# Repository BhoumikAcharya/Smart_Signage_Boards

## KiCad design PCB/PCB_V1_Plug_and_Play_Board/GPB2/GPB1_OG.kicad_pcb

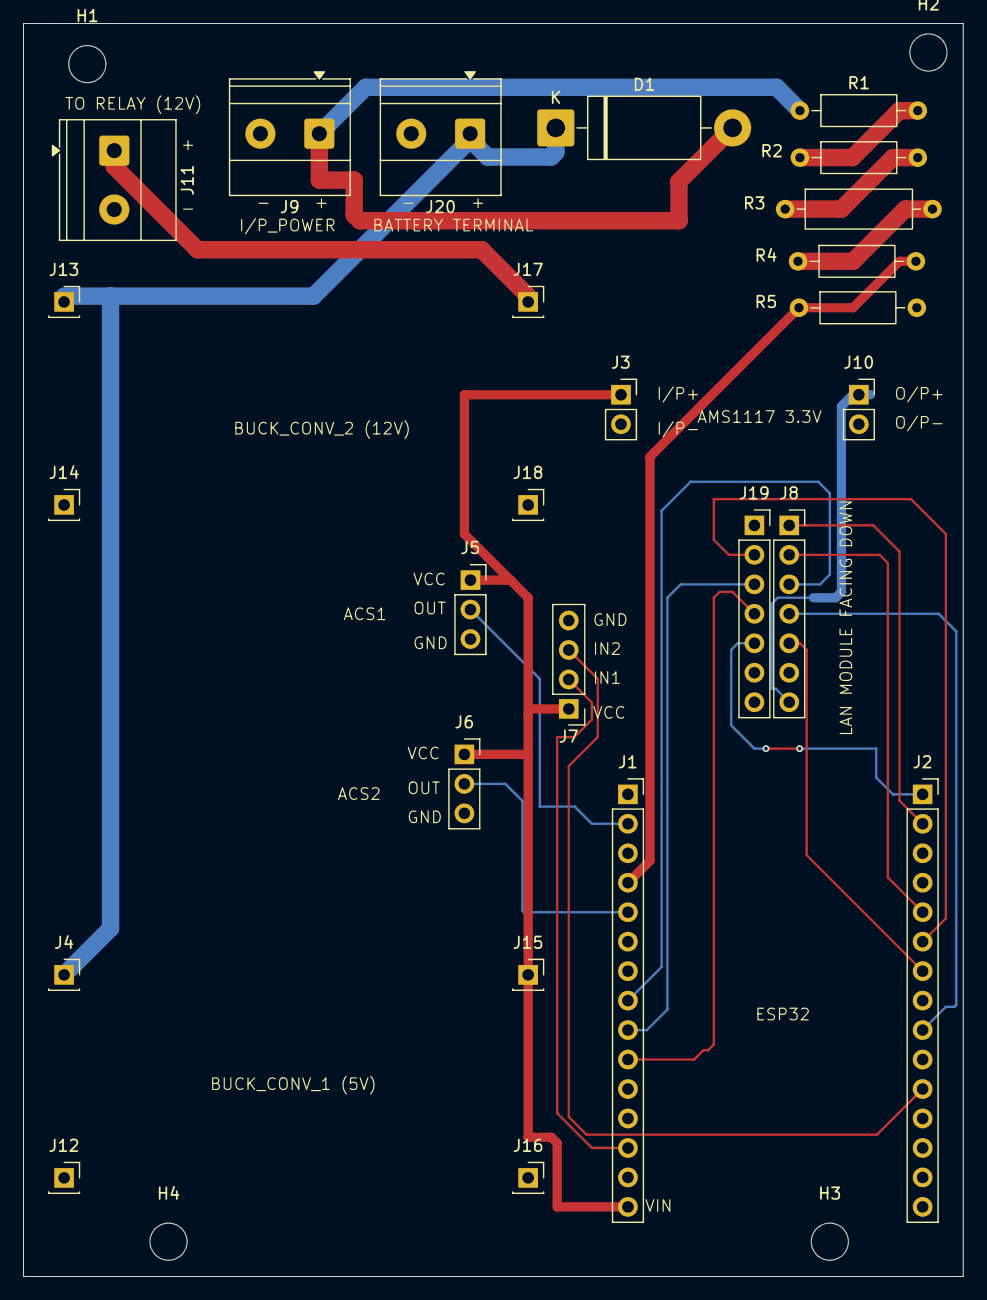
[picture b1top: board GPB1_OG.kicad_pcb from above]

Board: 2 copper layers, 81.0 x 108.0 mm, 30 parts (0 on the bottom side), 22 nets.

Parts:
D1: 1N5822; D_DO-201AD_P15.24mm_Horizontal
H1, H2, H3, H4: MountingScrew; MountingHole_3.2mm_M3
J1: ESP_Pins_1; PinSocket_1x15_P2.54mm_Vertical
J2: ESP_Pins_2; PinSocket_1x15_P2.54mm_Vertical
J3: AMS_I/P; PinSocket_1x02_P2.54mm_Vertical
J4: BC_I/P_+; PinSocket_1x01_P2.54mm_Vertical
J5: ACS712 1; PinSocket_1x03_P2.54mm_Vertical
J6: ACS712 2; PinSocket_1x03_P2.54mm_Vertical
J7: Relay; PinHeader_1x04_P2.54mm_Vertical
J8: LAN8720_Pins_1; PinSocket_1x07_P2.54mm_Vertical
J9, J20: I/P_TERMINAL; TerminalBlock_Phoenix_MKDS-1,5-2-5.08_1x02_P5.08mm_Horizont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
J10: AMS_O/P; PinSocket_1x02_P2.54mm_Vertical
J11: O/P Terminal; TerminalBlock_Phoenix_MKDS-1,5-2-5.08_1x02_P5.08mm_Horizont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
J12: BC1_I/P_GND; PinSocket_1x01_P2.54mm_Vertical
J13: BC2_I/P_+; PinSocket_1x01_P2.54mm_Vertical
J14: BC2_I/P_GND; PinSocket_1x01_P2.54mm_Vertical
J15: BC_O/P_+; PinSocket_1x01_P2.54mm_Vertical
J16: BC1_O/P_GND; PinSocket_1x01_P2.54mm_Vertical
J17: BC2_O/P_+; PinSocket_1x01_P2.54mm_Vertical
J18: BC2_O/P_GND; PinSocket_1x01_P2.54mm_Vertical
J19: LAN8720_Pins_2; PinSocket_1x07_P2.54mm_Vertical
R1, R2, R4, R5: 1K; R_Axial_DIN0207_L6.3mm_D2.5mm_P10.16mm_Horizontal
R3: 2.2K; R_Axial_DIN0309_L9.0mm_D3.2mm_P12.70mm_Horizontal

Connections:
+14.5V: D1.1 (K), D1.2 (A), J4.1, J9.1 (V+), J13.1, J20.1 (V+), R1.1
ACS_1: J1.2 (Vp), J5.2 (OUT)
ACS_2: J1.5 (D35), J6.2 (OUT)
AMS_O+: J8.7, J10.1 (O+)
BC1_O+: J1.15 (VIN), J3.1 (I+), J5.1 (VCC), J6.1 (VCC), J7.1 (VCC), J15.1
BC2_O+: J11.1 (V+), J17.1
CRS: J1.10 (D27), J19.4
GND: J1.14 (GND), J3.2 (GND), J5.3 (GND), J6.3 (GND), J7.4 (GND), J8.6, J9.2 (V-), J10.2 (GND), J11.2 (V-), J12.1, J14.1, J16.1, J18.1, J20.2 (V-), R5.2
IN1: J1.13 (D13), J7.2 (IN2)
IN2: J2.11 (D4), J7.3 (IN1)
MDC: J2.1 (D23), J19.5
MDIO: J2.7 (D18), J8.5
unnamed: R1.2, R2.1
unnamed: R2.2, R3.1
unnamed: R3.2, R4.1
RX1: J1.9 (D26), J19.3
RXO: J1.8 (D25), J8.3
TX0: J2.6 (D19), J19.2
TX1: J2.2 (D22), J8.1
TX_EN: J2.5 (D21), J8.2
V.D: J1.4 (D34), R4.2, R5.1
nINT: J2.9 (TX2), J8.4
